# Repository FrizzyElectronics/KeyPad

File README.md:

# KeyPad
The Keypad module carries 4 push buttons and uses 4 different values resistors to indicate which buttons are pressed. Four buttons using only one pin on your Arduino! With just an analogRead call you can know the button. The Keypad is great for greating game controllers in combination with 3D printing.

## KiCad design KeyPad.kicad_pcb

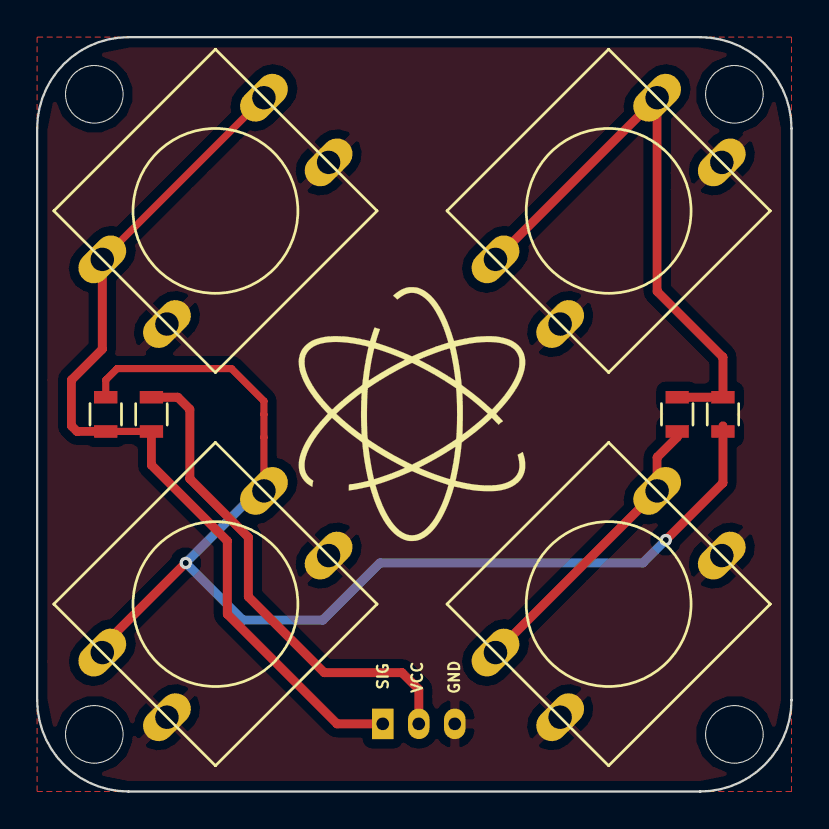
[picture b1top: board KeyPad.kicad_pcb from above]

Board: 2 copper layers, 41.9 x 41.9 mm, 9 parts (0 on the bottom side), 6 nets.

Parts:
P1: CONN_01X03; JST_PH_S3B-PH-K_03x2.00mm_Angled
R1: 2K; R_0805
R2: 330R; R_0805
R3: 620R; R_0805
R4: 1K; R_0805
SW1, SW2, SW3, SW4: SW_Push_Dual; SW_PUSH-12mm

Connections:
GND: P1.3, SW1.2, SW2.2, SW3.2, SW4.2
unnamed: P1.1, R1.2, R2.1, SW1.1
unnamed: R2.2, R3.1, SW2.1
unnamed: R3.2, R4.1, SW3.1
unnamed: R4.2, SW4.1
VCC: P1.2, R1.1

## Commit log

2017-04-14 License Added
2017-04-14 Esquematico terminado, DRC pasado y anotaciones echas
2017-04-16 Pcb enrrutada y esquinas redondeadas
2017-04-16 Error del conector reparado
2017-04-16 Version final, taladros añadidos, serigrafia lista
2017-05-14 Taladros reparados, los anteriores eran muy pequeños
2017-05-14 Mandado a fabrica
2017-05-27 Logos
    Small and big logos for the board
2018-01-08 archivos estandarizados para compartir
2018-01-10 3D añadido
2018-02-10 conector cambiado
2018-02-12 Logo cambiado
2018-02-24 Logos cambiados
2018-03-03 Arbol de carpetas cambiado
2018-03-03 Auto stash before merge of "master" and "origin/master"
2018-03-12 Added board render
2018-03-12 Added board render image to readme
2018-03-12 Board render added
2018-04-29 PDF exportado y carpeta keypad borrada
2018-05-06 BOM exportado
2018-07-15 Gerbers exportados
